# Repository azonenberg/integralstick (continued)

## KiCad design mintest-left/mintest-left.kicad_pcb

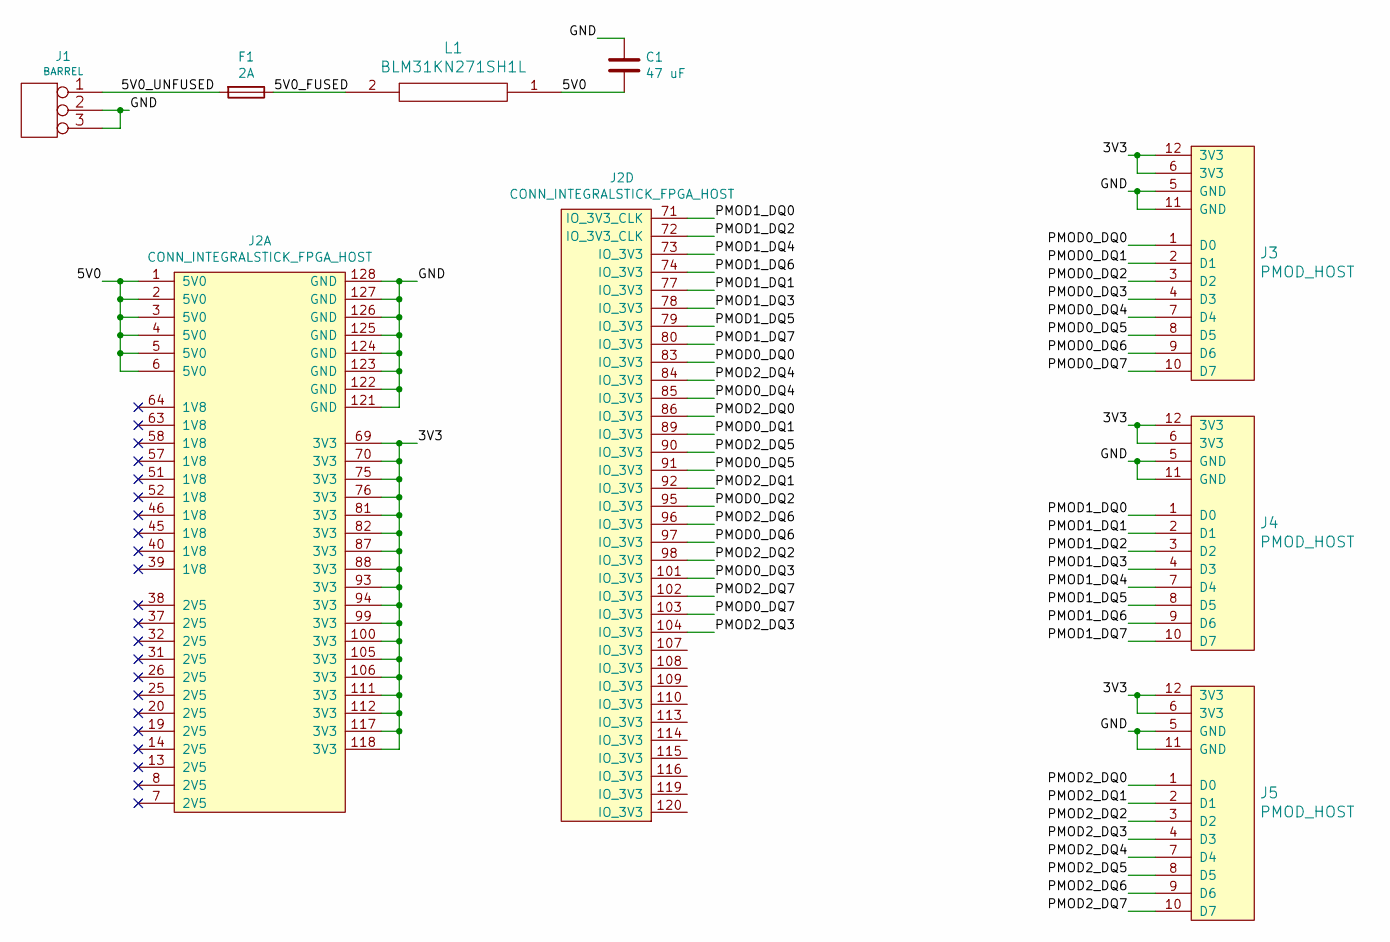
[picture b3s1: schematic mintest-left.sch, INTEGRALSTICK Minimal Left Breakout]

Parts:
C1: 47 uF; EIA_1210_CAP_NOSILK
F1: 2A; EIA_0603_CAP_NOSILK
J1: BARREL; CONN_CUI_PJ-058BH_HIPWR_BARREL_NOSLOT
J2: CONN_INTEGRALSTICK_FPGA_HOST; CONN_SAMTEC_QSH-060-01-L-D-A
J3, J4, J5: PMOD_HOST; CONN_HEADER_2.54MM_2x6_RA_PMOD_HOST
L1: BLM31KN271SH1L; EIA_1206_CAP_NOSILK

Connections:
/3V3: J2.69 (3V3), J2.70 (3V3), J2.75 (3V3), J2.76 (3V3), J2.81 (3V3), J2.82 (3V3), J2.87 (3V3), J2.88 (3V3), J2.93 (3V3), J2.94 (3V3), J2.99 (3V3), J2.100 (3V3), J2.105 (3V3), J2.106 (3V3), J2.111 (3V3), J2.112 (3V3), J2.117 (3V3), J2.118 (3V3), J3.6 (3V3), J3.12 (3V3), J4.6 (3V3), J4.12 (3V3), J5.6 (3V3), J5.12 (3V3)
/5V0: C1.2, J2.1 (5V0), J2.2 (5V0), J2.3 (5V0), J2.4 (5V0), J2.5 (5V0), J2.6 (5V0), L1.1
/5V0_FUSED: F1.1, L1.2
/5V0_UNFUSED: F1.2, J1.1
/GND: C1.1, J1.2 (PM), J1.3, J2.121 (GND), J2.122 (GND), J2.123 (GND), J2.124 (GND), J2.125 (GND), J2.126 (GND), J2.127 (GND), J2.128 (GND), J3.5 (GND), J3.11 (GND), J4.5 (GND), J4.11 (GND), J5.5 (GND), J5.11 (GND)
/PMOD0_DQ0: J2.83 (IO_3V3), J3.1 (D0)
/PMOD0_DQ1: J2.89 (IO_3V3), J3.2 (D1)
/PMOD0_DQ2: J2.95 (IO_3V3), J3.3 (D2)
/PMOD0_DQ3: J2.101 (IO_3V3), J3.4 (D3)
/PMOD0_DQ4: J2.85 (IO_3V3), J3.7 (D4)
/PMOD0_DQ5: J2.91 (IO_3V3), J3.8 (D5)
/PMOD0_DQ6: J2.97 (IO_3V3), J3.9 (D6)
/PMOD0_DQ7: J2.103 (IO_3V3), J3.10 (D7)
/PMOD1_DQ0: J2.71 (IO_3V3_CLK), J4.1 (D0)
/PMOD1_DQ1: J2.77 (IO_3V3), J4.2 (D1)
/PMOD1_DQ2: J2.72 (IO_3V3_CLK), J4.3 (D2)
/PMOD1_DQ3: J2.78 (IO_3V3), J4.4 (D3)
/PMOD1_DQ4: J2.73 (IO_3V3), J4.7 (D4)
/PMOD1_DQ5: J2.79 (IO_3V3), J4.8 (D5)
/PMOD1_DQ6: J2.74 (IO_3V3), J4.9 (D6)
/PMOD1_DQ7: J2.80 (IO_3V3), J4.10 (D7)
/PMOD2_DQ0: J2.86 (IO_3V3), J5.1 (D0)
/PMOD2_DQ1: J2.92 (IO_3V3), J5.2 (D1)
/PMOD2_DQ2: J2.98 (IO_3V3), J5.3 (D2)
/PMOD2_DQ3: J2.104 (IO_3V3), J5.4 (D3)
/PMOD2_DQ4: J2.84 (IO_3V3), J5.7 (D4)
/PMOD2_DQ5: J2.90 (IO_3V3), J5.8 (D5)
/PMOD2_DQ6: J2.96 (IO_3V3), J5.9 (D6)
/PMOD2_DQ7: J2.102 (IO_3V3), J5.10 (D7)

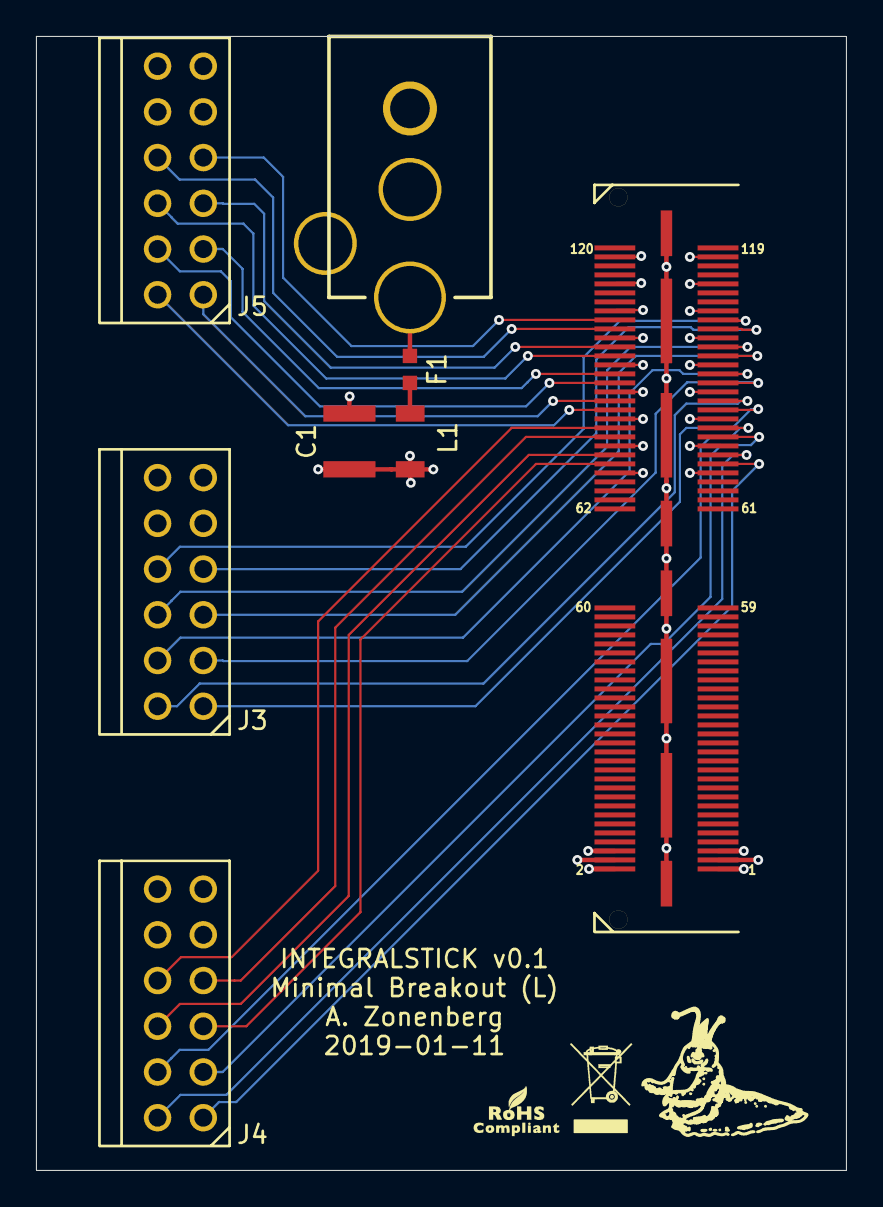
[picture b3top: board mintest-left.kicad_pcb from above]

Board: 4 copper layers, 45.0 x 63.0 mm, 8 parts (0 on the bottom side), 29 nets.

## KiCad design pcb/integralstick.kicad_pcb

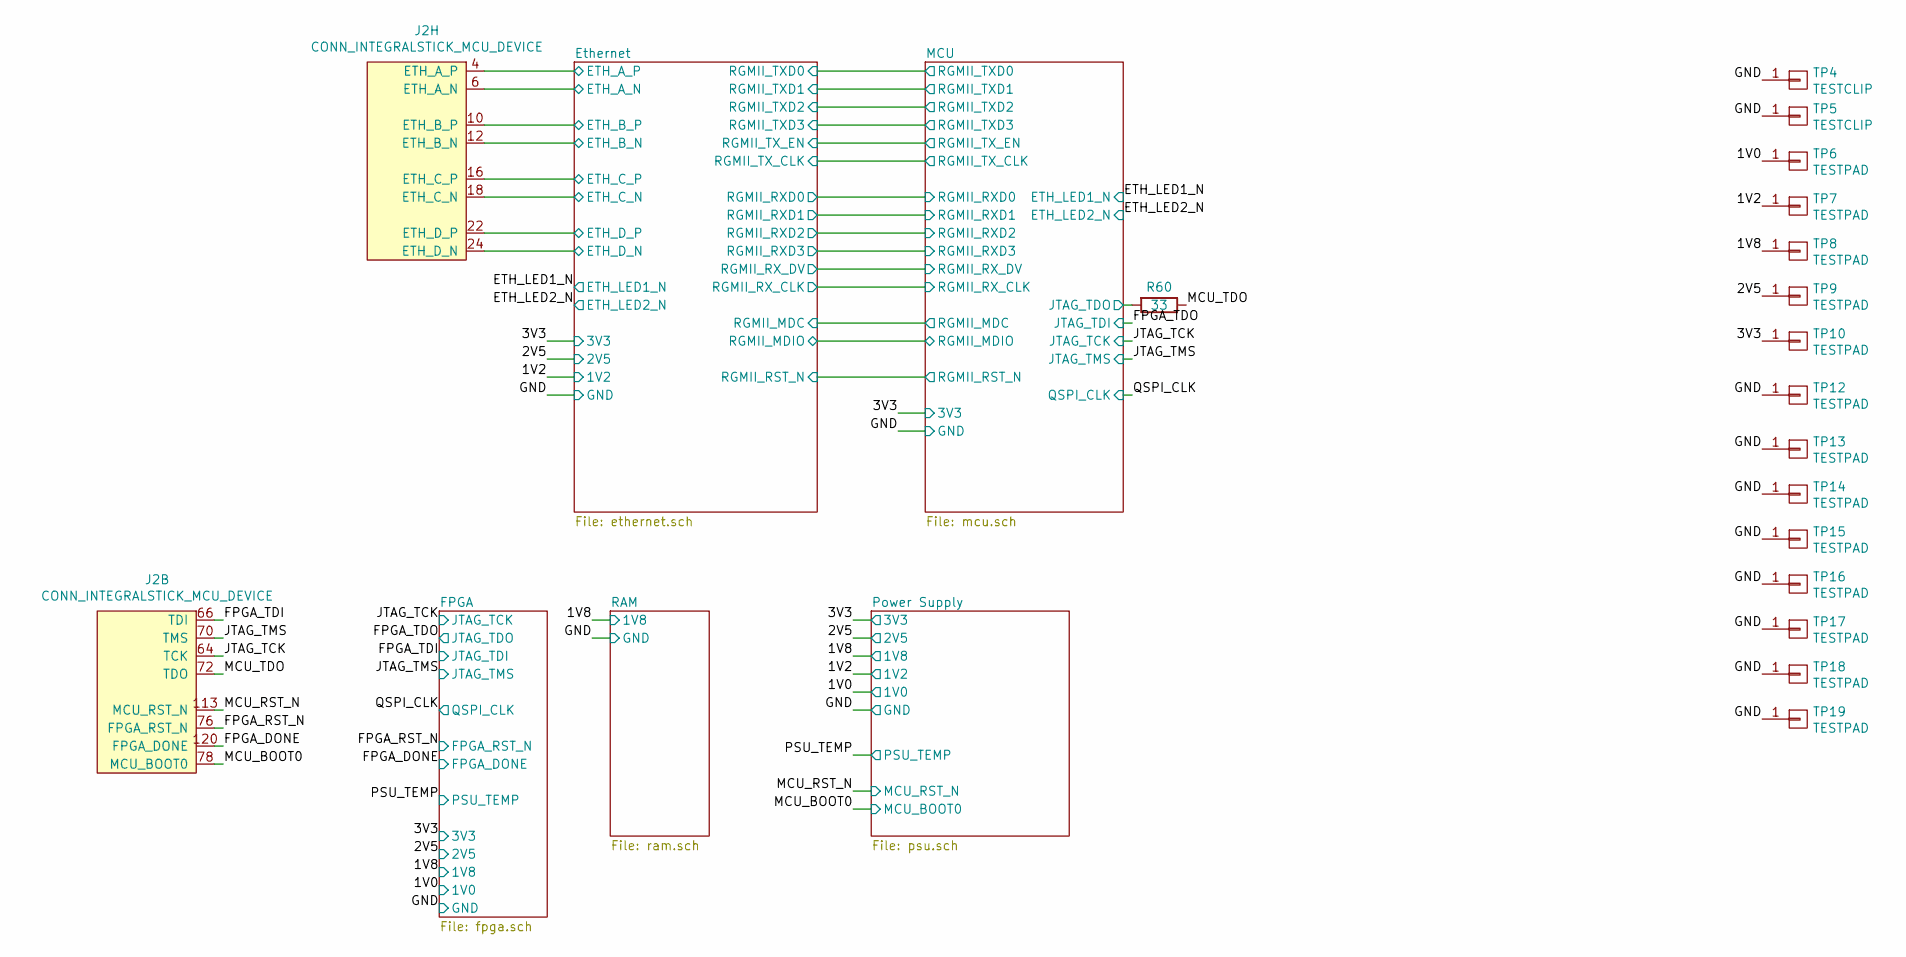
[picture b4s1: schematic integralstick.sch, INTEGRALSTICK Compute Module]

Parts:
J2: CONN_INTEGRALSTICK_MCU_DEVICE; CONN_SAMTEC_QTH-060-01-L-D-A
R60: 33; EIA_0402_RES_NOSILK
TP4, TP5: TESTCLIP; TESTPOINT_SMT_KEYSTONE_5016
TP6, TP7, TP8, TP9, TP10: TESTPAD; TESTPOINT_SMT_0.5MM
TP12, TP13, TP14, TP15, TP16, TP17, TP18, TP19: TESTPAD; TESTPOINT_BARETRACE_328UM

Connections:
/1V0: TP6.1; also elsewhere on the board
/1V2: TP7.1; also elsewhere on the board
/1V8: TP8.1; also elsewhere on the board
/2V5: TP9.1; also elsewhere on the board
/3V3: TP10.1; also elsewhere on the board
/Ethernet/ETH_A_N: J2.6 (ETH_A_N); also elsewhere on the board
/Ethernet/ETH_A_P: J2.4 (ETH_A_P); also elsewhere on the board
/Ethernet/ETH_B_N: J2.12 (ETH_B_N); also elsewhere on the board
/Ethernet/ETH_B_P: J2.10 (ETH_B_P); also elsewhere on the board
/Ethernet/ETH_C_N: J2.18 (ETH_C_N); also elsewhere on the board
/Ethernet/ETH_C_P: J2.16 (ETH_C_P); also elsewhere on the board
/Ethernet/ETH_D_N: J2.24 (ETH_D_N); also elsewhere on the board
/Ethernet/ETH_D_P: J2.22 (ETH_D_P); also elsewhere on the board
/FPGA_DONE: J2.120 (FPGA_DONE); also elsewhere on the board
/FPGA_RST_N: J2.76 (FPGA_RST_N); also elsewhere on the board
/FPGA_TDI: J2.66 (TDI); also elsewhere on the board
/GND: TP4.1, TP5.1, TP12.1, TP13.1, TP14.1, TP15.1, TP16.1, TP17.1, TP18.1, TP19.1; also elsewhere on the board
/JTAG_TCK: J2.64 (TCK); also elsewhere on the board
/JTAG_TMS: J2.70 (TMS); also elsewhere on the board
/MCU/JTAG_TDO: R60.2; also elsewhere on the board
/MCU_BOOT0: J2.78 (MCU_BOOT0); also elsewhere on the board
/MCU_RST_N: J2.113 (MCU_RST_N); also elsewhere on the board
/MCU_TDO: J2.72 (TDO), R60.1

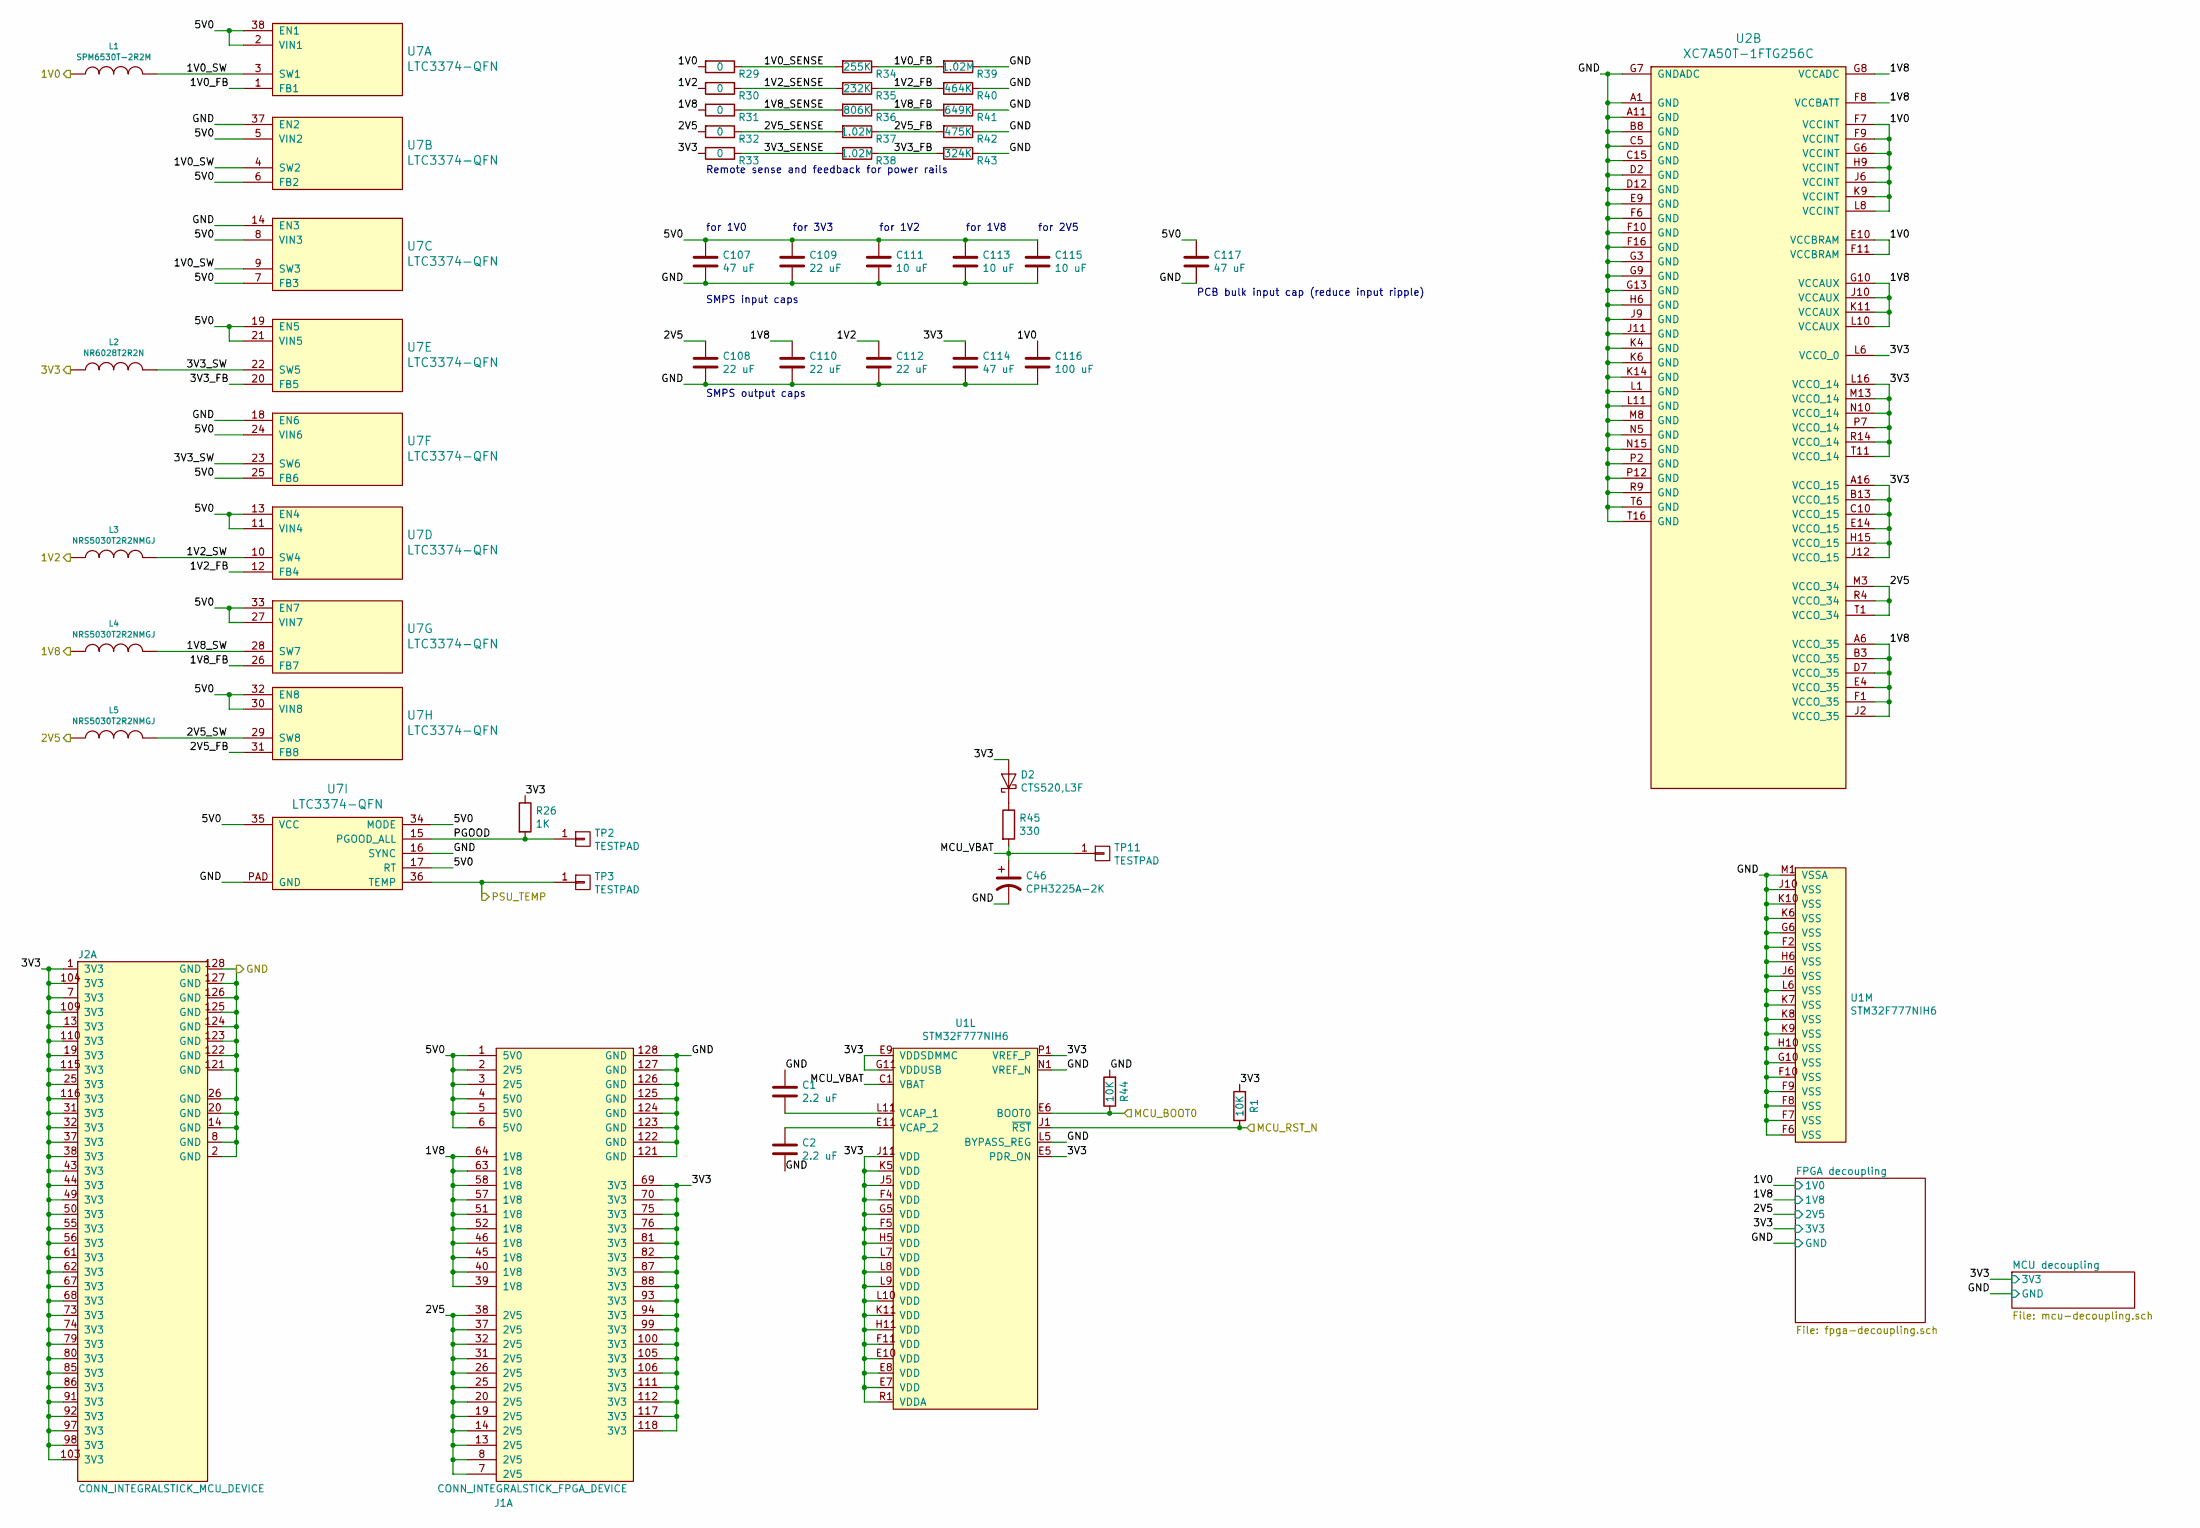
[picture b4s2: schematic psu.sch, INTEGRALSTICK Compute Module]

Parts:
C1, C2: 2.2 uF; EIA_0603_CAP_NOSILK
C46: CPH3225A-2K; CAP_SEIKO_CPH3225A
C107, C114, C117: 47 uF; EIA_1210_CAP_NOSILK
C108, C109, C110, C112: 22 uF; EIA_1206_CAP_NOSILK
C111, C113, C115: 10 uF; EIA_1206_CAP_NOSILK
C116: 100 uF; EIA_1210_CAP_NOSILK
D2: CTS520,L3F‎; SOD882
J1: CONN_INTEGRALSTICK_FPGA_DEVICE; CONN_SAMTEC_QTH-060-01-L-D-A
J2: CONN_INTEGRALSTICK_MCU_DEVICE; CONN_SAMTEC_QTH-060-01-L-D-A
L1: SPM6530T-2R2M; INDUCTOR_TDK_SPM6530
L2: NR6028T2R2N; INDUCTOR_YUDEN_NR6028
L3, L4, L5: NRS5030T2R2NMGJ; INDUCTOR_YUDEN_NRS5030
R1, R44: 10K; EIA_0402_RES_NOSILK
R26: 1K; EIA_0402_RES_NOSILK
R29, R30, R31, R32, R33: 0; EIA_0402_RES_NOSILK
R34: 255K; EIA_0402_RES_NOSILK
R35: 232K; EIA_0402_RES_NOSILK
R36: 806K; EIA_0402_RES_NOSILK
R37, R38, R39: 1.02M; EIA_0402_RES_NOSILK
R40: 464K; EIA_0402_RES_NOSILK
R41: 649K; EIA_0402_RES_NOSILK
R42: 475K; EIA_0402_RES_NOSILK
R43: 324K; EIA_0402_RES_NOSILK
R45: 330; EIA_0402_RES_NOSILK
TP2, TP3, TP11: TESTPAD; TESTPOINT_SMT_0.5MM
U1: STM32F777NIH6‎; BGA_216_13x13_DEPOP3x3_0.8MM
U2: XC7A50T-1FTG256C; BGA_256_17x17_FULLARRAY_1MM_0.4MM_FTG256
U7: LTC3374-QFN; QFN_38_0.5MM_5x7MM

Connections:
/1V0: C116.1, L1.1, R29.2, U2.E10 (VCCBRAM), U2.F7 (VCCINT), U2.F9 (VCCINT), U2.F11 (VCCBRAM), U2.G6 (VCCINT), U2.H9 (VCCINT), U2.J6 (VCCINT), U2.K9 (VCCINT), U2.L8 (VCCINT); also elsewhere on the board
/1V2: C112.1, L3.1, R30.2; also elsewhere on the board
/1V8: C110.1, J1.39 (1V8), J1.40 (1V8), J1.45 (1V8), J1.46 (1V8), J1.51 (1V8), J1.52 (1V8), J1.57 (1V8), J1.58 (1V8), J1.63 (1V8), J1.64 (1V8), L4.1, R31.2, U2.A6 (VCCO_35), U2.B3 (VCCO_35), U2.D7 (VCCO_35), U2.E4 (VCCO_35), U2.F1 (VCCO_35), U2.F8 (VCCBATT), U2.G8 (VCCADC), U2.G10 (VCCAUX), U2.J2 (VCCO_35), U2.J10 (VCCAUX), U2.K11 (VCCAUX), U2.L10 (VCCAUX); also elsewhere on the board
/2V5: C108.1, J1.7 (2V5), J1.8 (2V5), J1.13 (2V5), J1.14 (2V5), J1.19 (2V5), J1.20 (2V5), J1.25 (2V5), J1.26 (2V5), J1.31 (2V5), J1.32 (2V5), J1.37 (2V5), J1.38 (2V5), L5.1, R32.2, U2.M3 (VCCO_34), U2.R4 (VCCO_34), U2.T1 (VCCO_34); also elsewhere on the board
/3V3: C114.1, D2.2 (A), J1.69 (3V3), J1.70 (3V3), J1.75 (3V3), J1.76 (3V3), J1.81 (3V3), J1.82 (3V3), J1.87 (3V3), J1.88 (3V3), J1.93 (3V3), J1.94 (3V3), J1.99 (3V3), J1.100 (3V3), J1.105 (3V3), J1.106 (3V3), J1.111 (3V3), J1.112 (3V3), J1.117 (3V3), J1.118 (3V3), J2.1 (3V3), J2.7 (3V3), J2.13 (3V3), J2.19 (3V3), J2.25 (3V3), J2.31 (3V3), J2.32 (3V3), J2.37 (3V3), J2.38 (3V3), J2.43 (3V3), J2.44 (3V3), J2.49 (3V3), J2.50 (3V3), J2.55 (3V3), J2.56 (3V3), J2.61 (3V3), J2.62 (3V3), J2.67 (3V3), J2.68 (3V3), J2.73 (3V3), J2.74 (3V3), J2.79 (3V3), J2.80 (3V3), J2.85 (3V3), J2.86 (3V3), J2.91 (3V3), J2.92 (3V3), J2.97 (3V3), J2.98 (3V3), J2.103 (3V3), J2.104 (3V3), J2.109 (3V3), J2.110 (3V3), J2.115 (3V3), J2.116 (3V3), L2.1, R1.2, R26.1, R33.2, U1.E5 (PDR_ON), U1.E7 (VDD), U1.E8 (VDD), U1.E9 (VDDSDMMC), U1.E10 (VDD), U1.F4 (VDD), U1.F5 (VDD), U1.F11 (VDD), U1.G5 (VDD), U1.G11 (VDDUSB), U1.H5 (VDD), U1.H11 (VDD), U1.J5 (VDD), U1.J11 (VDD), U1.K5 (VDD), U1.K11 (VDD), U1.L7 (VDD), U1.L8 (VDD), U1.L9 (VDD), U1.L10 (VDD), U1.P1 (VREF_P), U1.R1 (VDDA), U2.A16 (VCCO_15), U2.B13 (VCCO_15), U2.C10 (VCCO_15), U2.E14 (VCCO_15), U2.H15 (VCCO_15), U2.J12 (VCCO_15), U2.L6 (VCCO_0), U2.L16 (VCCO_14), U2.M13 (VCCO_14), U2.N10 (VCCO_14), U2.P7 (VCCO_14), U2.R14 (VCCO_14), U2.T11 (VCCO_14); also elsewhere on the board
/GND: C1.1, C2.2, C46.2, C107.2, C108.2, C109.2, C110.2, C111.2, C112.2, C113.2, C114.2, C115.2, C116.2, C117.2, J1.121 (GND), J1.122 (GND), J1.123 (GND), J1.124 (GND), J1.125 (GND), J1.126 (GND), J1.127 (GND), J1.128 (GND), J2.2 (GND), J2.8 (GND), J2.14 (GND), J2.20 (GND), J2.26 (GND), J2.121 (GND), J2.122 (GND), J2.123 (GND), J2.124 (GND), J2.125 (GND), J2.126 (GND), J2.127 (GND), J2.128 (GND), R39.1, R40.1, R41.1, R42.1, R43.1, R44.2, U1.F2 (VSS), U1.F6 (VSS), U1.F7 (VSS), U1.F8 (VSS), U1.F9 (VSS), U1.F10 (VSS), U1.G6 (VSS), U1.G10 (VSS), U1.H6 (VSS), U1.H10 (VSS), U1.J6 (VSS), U1.J10 (VSS), U1.K6 (VSS), U1.K7 (VSS), U1.K8 (VSS), U1.K9 (VSS), U1.K10 (VSS), U1.L5 (BYPASS_REG), U1.L6 (VSS), U1.M1 (VSSA), U1.N1 (VREF_N), U2.A1 (GND), U2.A11 (GND), U2.B8 (GND), U2.C5 (GND), U2.C15 (GND), U2.D2 (GND), U2.D12 (GND), U2.E9 (GND), U2.F6 (GND), U2.F10 (GND), U2.F16 (GND), U2.G3 (GND), U2.G7 (GNDADC), U2.G9 (GND), U2.G13 (GND), U2.H6 (GND), U2.J9 (GND), U2.J11 (GND), U2.K4 (GND), U2.K6 (GND), U2.K14 (GND), U2.L1 (GND), U2.L11 (GND), U2.M8 (GND), U2.N5 (GND), U2.N15 (GND), U2.P2 (GND), U2.P12 (GND), U2.R9 (GND), U2.T6 (GND), U2.T16 (GND), U7.14 (EN3), U7.16 (SYNC), U7.18 (EN6), U7.37 (EN2), U7.PAD (GND); also elsewhere on the board
/MCU_BOOT0: R44.1, U1.E6 (BOOT0); also elsewhere on the board
/MCU_RST_N: R1.1, U1.J1 (~RST); also elsewhere on the board
/PSU_TEMP: TP3.1, U7.36 (TEMP); also elsewhere on the board
/Power Supply/1V0_FB: R34.1, R39.2, U7.1 (FB1)
/Power Supply/1V0_SENSE: R29.1, R34.2
/Power Supply/1V0_SW: L1.2, U7.3 (SW1), U7.4 (SW2), U7.9 (SW3)
/Power Supply/1V2_FB: R35.1, R40.2, U7.12 (FB4)
/Power Supply/1V2_SENSE: R30.1, R35.2
/Power Supply/1V2_SW: L3.2, U7.10 (SW4)
/Power Supply/1V8_FB: R36.1, R41.2, U7.26 (FB7)
/Power Supply/1V8_SENSE: R31.1, R36.2
/Power Supply/1V8_SW: L4.2, U7.28 (SW7)
/Power Supply/2V5_FB: R37.1, R42.2, U7.31 (FB8)
/Power Supply/2V5_SENSE: R32.1, R37.2
/Power Supply/2V5_SW: L5.2, U7.29 (SW8)
/Power Supply/3V3_FB: R38.1, R43.2, U7.20 (FB5)
/Power Supply/3V3_SENSE: R33.1, R38.2
/Power Supply/3V3_SW: L2.2, U7.22 (SW5), U7.23 (SW6)
/Power Supply/5V0: C107.1, C109.1, C111.1, C113.1, C115.1, C117.1, J1.1 (5V0), J1.2 (2V5), J1.3 (2V5), J1.4 (5V0), J1.5 (5V0), J1.6 (5V0), U7.2 (VIN1), U7.5 (VIN2), U7.6 (FB2), U7.7 (FB3), U7.8 (VIN3), U7.11 (VIN4), U7.13 (EN4), U7.17 (RT), U7.19 (EN5), U7.21 (VIN5), U7.24 (VIN6), U7.25 (FB6), U7.27 (VIN7), U7.30 (VIN8), U7.32 (EN8), U7.33 (EN7), U7.34 (MODE), U7.35 (VCC), U7.38 (EN1)
/Power Supply/MCU_VBAT: C46.1, R45.2, TP11.1, U1.C1 (VBAT)
/Power Supply/PGOOD: R26.2, TP2.1, U7.15 (PGOOD_ALL)
unnamed: C1.2, U1.L11 (VCAP_1)
unnamed: C2.1, U1.E11 (VCAP_2)
unnamed: D2.1 (K), R45.1

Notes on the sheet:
SMPS input caps
Remote sense and feedback for power rails
for 1V0
for 3V3
for 1V2
for 1V8
for 2V5
PCB bulk input cap (reduce input ripple)
SMPS output caps

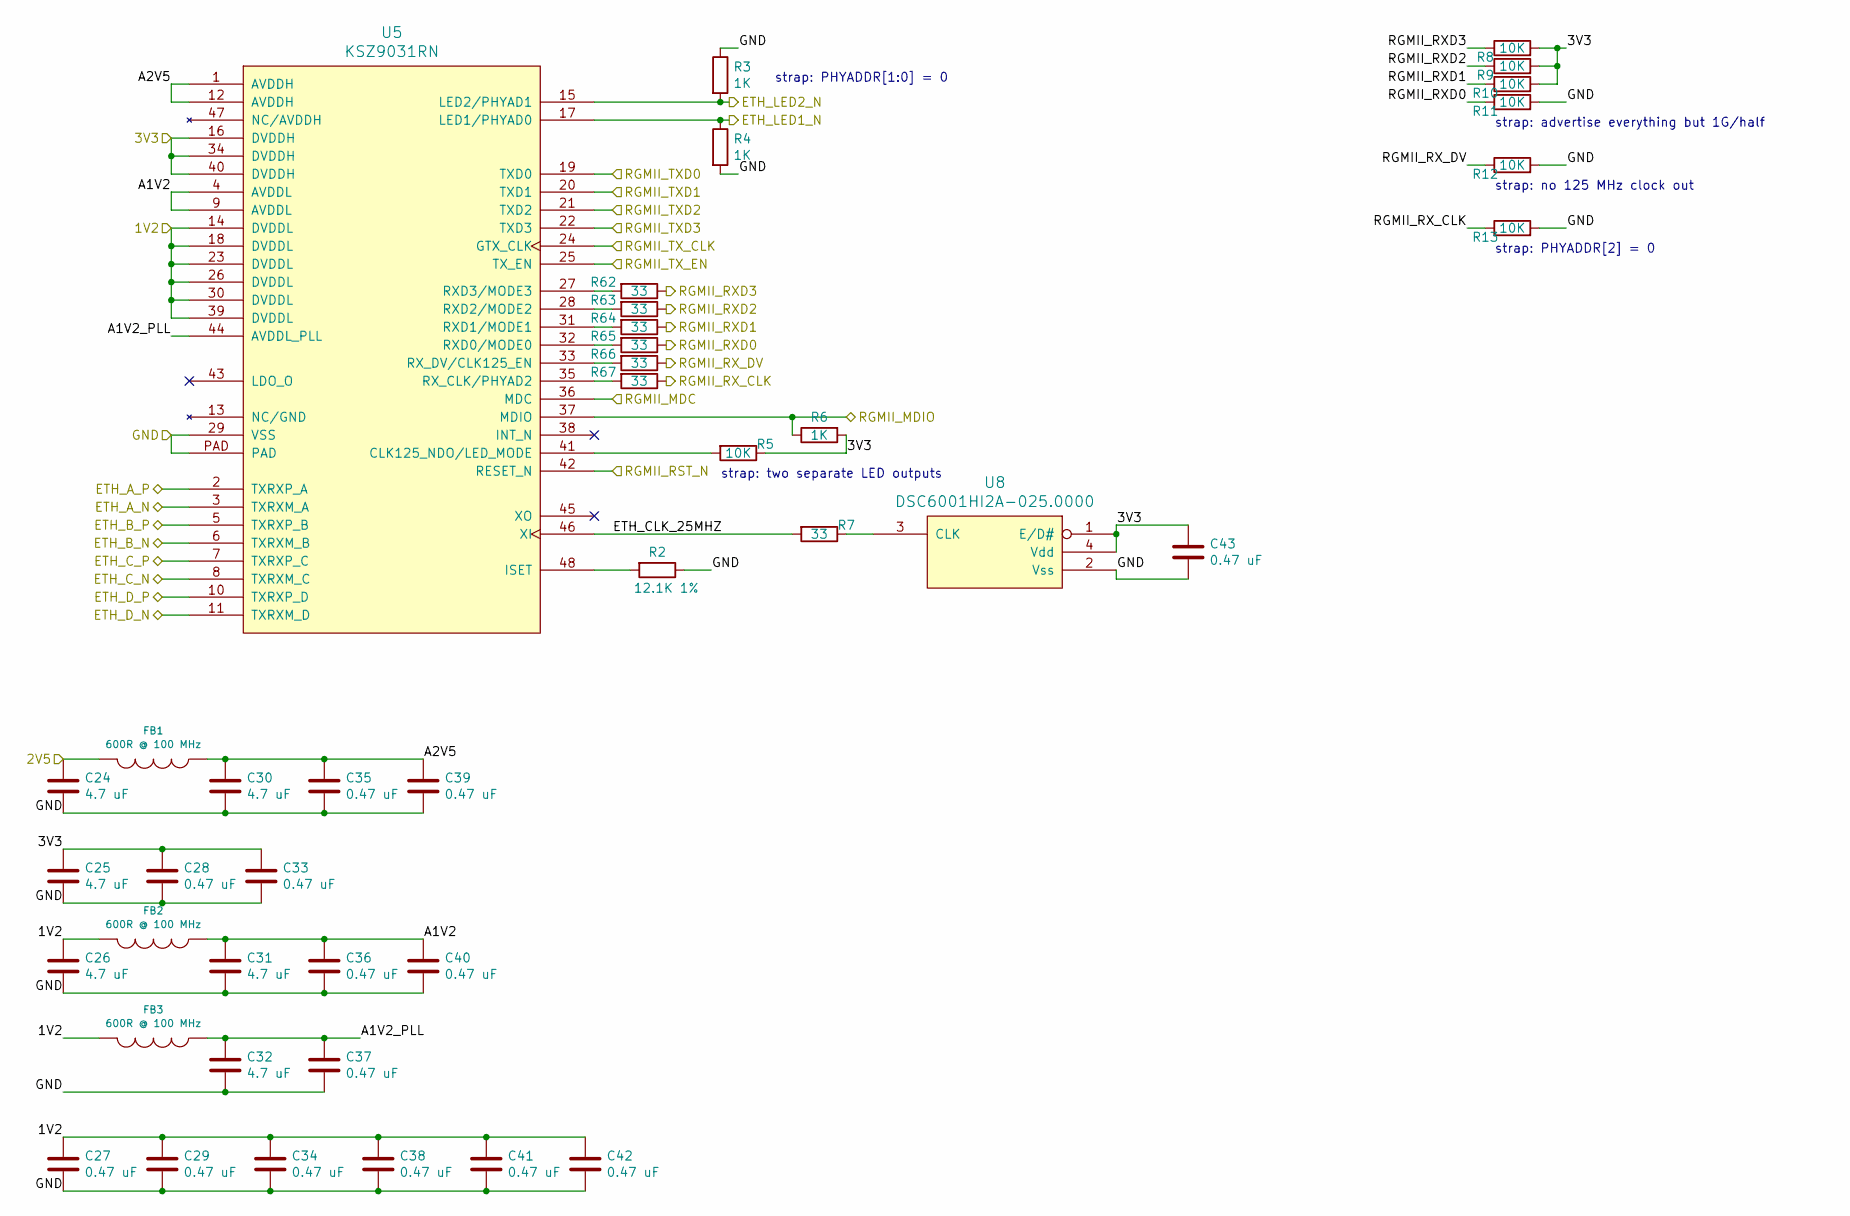
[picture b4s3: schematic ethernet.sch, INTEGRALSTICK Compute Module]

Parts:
C24, C25, C26, C30, C31, C32: 4.7 uF; EIA_0603_CAP_NOSILK
C27, C28, C29, C33, C34, C35, C36, C37, C38, C39, C40, C41, C42, C43: 0.47 uF; EIA_0402_CAP_NOSILK
FB1, FB2, FB3: 600R @ 100 MHz; EIA_0402_CAP_NOSILK
R2: 12.1K 1%; EIA_0402_RES_NOSILK
R3, R4, R6: 1K; EIA_0402_RES_NOSILK
R5, R8, R9, R10, R11, R12, R13: 10K; EIA_0402_RES_NOSILK
R7, R62, R63, R64, R65, R66, R67: 33; EIA_0402_RES_NOSILK
U5: KSZ9031RN; QFN_48_0.5MM_7x7MM
U8: DSC6001HI2A-025.0000; OSCILLATOR_1.6x1.2

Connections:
/1V2: C26.1, C27.1, C29.1, C34.1, C38.1, C41.1, C42.1, FB2.2, FB3.2, U5.14 (DVDDL), U5.18 (DVDDL), U5.23 (DVDDL), U5.26 (DVDDL), U5.30 (DVDDL), U5.39 (DVDDL); also elsewhere on the board
/2V5: C24.1, FB1.2; also elsewhere on the board
/3V3: C25.1, C28.1, C33.1, C43.1, R5.1, R6.2, R8.2, R9.2, R10.2, U5.16 (DVDDH), U5.34 (DVDDH), U5.40 (DVDDH), U8.1 (E/D#), U8.4 (Vdd); also elsewhere on the board
/ETH_LED1_N: R4.1, U5.17 (LED1/PHYAD0); also elsewhere on the board
/ETH_LED2_N: R3.2, U5.15 (LED2/PHYAD1); also elsewhere on the board
/Ethernet/A1V2: C31.1, C36.1, C40.1, FB2.1, U5.4 (AVDDL), U5.9 (AVDDL)
/Ethernet/A1V2_PLL: C32.1, C37.1, FB3.1, U5.44 (AVDDL_PLL)
/Ethernet/A2V5: C30.1, C35.1, C39.1, FB1.1, U5.1 (AVDDH), U5.12 (AVDDH)
/Ethernet/ETH_A_N: U5.3 (TXRXM_A); also elsewhere on the board
/Ethernet/ETH_A_P: U5.2 (TXRXP_A); also elsewhere on the board
/Ethernet/ETH_B_N: U5.6 (TXRXM_B); also elsewhere on the board
/Ethernet/ETH_B_P: U5.5 (TXRXP_B); also elsewhere on the board
/Ethernet/ETH_CLK_25MHZ: R7.2, U5.46 (XI)
/Ethernet/ETH_C_N: U5.8 (TXRXM_C); also elsewhere on the board
/Ethernet/ETH_C_P: U5.7 (TXRXP_C); also elsewhere on the board
/Ethernet/ETH_D_N: U5.11 (TXRXM_D); also elsewhere on the board
/Ethernet/ETH_D_P: U5.10 (TXRXP_D); also elsewhere on the board
/Ethernet/RGMII_MDC: U5.36 (MDC); also elsewhere on the board
/Ethernet/RGMII_MDIO: R6.1, U5.37 (MDIO); also elsewhere on the board
/Ethernet/RGMII_RST_N: U5.42 (RESET_N); also elsewhere on the board
/Ethernet/RGMII_RXD0: R11.1, R65.1; also elsewhere on the board
/Ethernet/RGMII_RXD1: R10.1, R64.1; also elsewhere on the board
/Ethernet/RGMII_RXD2: R9.1, R63.1; also elsewhere on the board
/Ethernet/RGMII_RXD3: R8.1, R62.1; also elsewhere on the board
/Ethernet/RGMII_RX_CLK: R13.1, R67.1; also elsewhere on the board
/Ethernet/RGMII_RX_DV: R12.1, R66.1; also elsewhere on the board
/Ethernet/RGMII_TXD0: U5.19 (TXD0); also elsewhere on the board
/Ethernet/RGMII_TXD1: U5.20 (TXD1); also elsewhere on the board
/Ethernet/RGMII_TXD2: U5.21 (TXD2); also elsewhere on the board
/Ethernet/RGMII_TXD3: U5.22 (TXD3); also elsewhere on the board
/Ethernet/RGMII_TX_CLK: U5.24 (GTX_CLK); also elsewhere on the board
/Ethernet/RGMII_TX_EN: U5.25 (TX_EN); also elsewhere on the board
/GND: C24.2, C25.2, C26.2, C27.2, C28.2, C29.2, C30.2, C31.2, C32.2, C33.2, C34.2, C35.2, C36.2, C37.2, C38.2, C39.2, C40.2, C41.2, C42.2, C43.2, R2.1, R3.1, R4.2, R11.2, R12.2, R13.2, U5.29 (VSS), U5.PAD, U8.2 (Vss); also elsewhere on the board
unnamed: R2.2, U5.48 (ISET)
unnamed: R5.2, U5.41 (CLK125_NDO/LED_MODE)
unnamed: R7.1, U8.3 (CLK)
unnamed: R62.2, U5.27 (RXD3/MODE3)
unnamed: R63.2, U5.28 (RXD2/MODE2)
unnamed: R64.2, U5.31 (RXD1/MODE1)
unnamed: R65.2, U5.32 (RXD0/MODE0)
unnamed: R66.2, U5.33 (RX_DV/CLK125_EN)
unnamed: R67.2, U5.35 (RX_CLK/PHYAD2)

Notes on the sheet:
strap: PHYADDR[1:0] = 0
strap: two separate LED outputs
strap: advertise everything but 1G/half
strap: no 125 MHz clock out
strap: PHYADDR[2] = 0
